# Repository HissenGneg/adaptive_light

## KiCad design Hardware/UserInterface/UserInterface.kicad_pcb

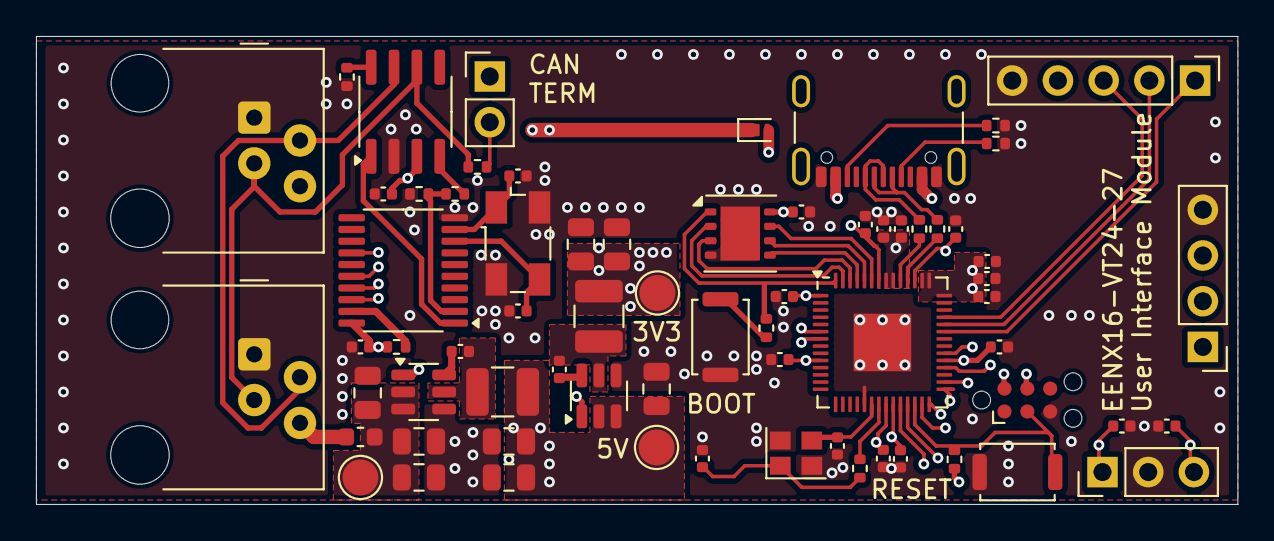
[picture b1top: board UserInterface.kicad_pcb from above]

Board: 4 copper layers, 66.8 x 26.0 mm, 68 parts (0 on the bottom side), 51 nets.

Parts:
C101, C102, C201, C202, C203, C204, C205, C206, C207, C208, C209, C211, C212, C213, C303, C304, C307, C311: 100n; C_0402_1005Metric
C210: 1u; C_0402_1005Metric
C214, C215, C305, C306: 10p; C_0402_1005Metric
C301, C302, C308, C312: 10u; C_0805_2012Metric
C309, C310, C313, C314: 22u; C_0805_2012Metric
D201: D_Schottky; Nexperia_DSN1608-2_1.6x0.8mm
F301: 4A; Fuse_0603_1608Metric
J101: conn_turnSignal; PinHeader_1x03_P2.54mm_Vertical
J102: conn_OLED; PinHeader_1x04_P2.54mm_Vertical
J103: conn_joystick; PinHeader_1x05_P2.54mm_Vertical
J201: TagConnect_SWD; Tag-Connect_TC2030-IDC-NL_2x03_P1.27mm_Vertical
J202: USB_C_Receptacle_USB2.0_16P; USB_C_Receptacle_GCT_USB4105-xx-A_16P_TopMnt_Horizontal
J301, J302: RJ9; RJ9_Evercom_5301-440xxx_Horizontal
JP301: Jumper_termination; PinHeader_1x02_P2.54mm_Vertical
L301, L302: 4u7; L_1210_3225Metric
R201, R202, R302: 5k1; R_0402_1005Metric
R203, R303, R304, R305: 10k; R_0402_1005Metric
R204, R207: 1k; R_0402_1005Metric
R205, R206: 27; R_0402_1005Metric
R301: 120; R_0402_1005Metric
SW201, SW202: SW_Push; SW_Push_SPST_NO_Alps_SKRK
TP301: TPVin; TestPoint_Pad_D2.0mm
TP302: TP3V3; TestPoint_Pad_D2.0mm
TP303: TP5V; TestPoint_Pad_D2.0mm
U201: W25Q64JVXGIQ; WSON-8-1EP_4x4mm_P0.8mm_EP2.2x3mm
U202: RP2040; QFN-56-1EP_7x7mm_P0.4mm_EP3.2x3.2mm
U301: MCP2551-I-SN; SOIC-8_3.9x4.9mm_P1.27mm
U302: MCP2515-xST; TSSOP-20_4.4x6.5mm_P0.65mm
U303: AP63203WU; TSOT-23-6
U304: AP63205WU; TSOT-23-6
Y201: 12M; Crystal_SMD_2520-4Pin_2.5x2.0mm
Y301: 8M; Crystal_SMD_Abracon_ABM3B-4Pin_5.0x3.2mm

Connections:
+1V1: C210.1, C211.1, C212.1, U202.23 (DVDD), U202.45 (VREG_VOUT), U202.50 (DVDD)
+3V3: C201.1, C202.1, C203.1, C204.1, C205.1, C206.1, C207.1, C208.1, C209.1, C213.1, C303.1, C309.1, C310.1, J102.3, J103.4, L301.2, R203.1, R305.1, TP302.1, U201.8 (VCC), U202.1 (IOVDD), U202.10 (IOVDD), U202.22 (IOVDD), U202.33 (IOVDD), U202.42 (IOVDD), U202.43 (ADC_AVDD), U202.44 (VREG_IN), U202.48 (USB_VDD), U202.49 (IOVDD), U302.20 (VDD), U303.1 (FB)
+5V: C304.1, C308.1, C313.1, C314.1, D201.1 (K), L302.2, TP303.1, U301.3 (VDD), U303.2 (EN), U303.3 (IN), U304.1 (FB)
+SYSTEM: C301.1, C302.1, C312.1, F301.2, TP301.1, U304.2 (EN), U304.3 (IN)
/BTN: J103.1, U202.37 (GPIO25)
/BTN_LEFT: C102.2, J101.3, U202.34 (GPIO22)
/BTN_RIGHT: C101.1, J101.1, U202.32 (GPIO21)
/CAN_Bus+power/CANH: J301.2, J302.2, JP301.1 (A), U301.7 (CANH)
/CAN_Bus+power/CANL: J301.3, J302.3, R301.2, U301.6 (CANL)
/MISO: U202.27 (GPIO16), U302.17 (SO)
/MOSI: U202.30 (GPIO19), U302.16 (SI)
/Microcontroller/FLASH_CLK: U201.6 (CLK), U202.52 (QSPI_SCLK)
/Microcontroller/FLASH_IO0: U201.5 (DI(IO0)), U202.53 (QSPI_SD0)
/Microcontroller/FLASH_IO1: U201.2 (DO(IO1)), U202.55 (QSPI_SD1)
/Microcontroller/FLASH_IO2: U201.3 (IO2), U202.54 (QSPI_SD2)
/Microcontroller/FLASH_IO3: U201.7 (IO3), U202.51 (QSPI_SD3)
/Microcontroller/FLASH_~CS: R204.2, U201.1 (~CS), U202.56 (QSPI_SS)
/Microcontroller/RP2040_D+: R205.2, U202.47 (USB_DP)
/Microcontroller/RP2040_D-: R206.2, U202.46 (USB_DM)
/Microcontroller/SWCLK: J201.4 (SWCLK), U202.24 (SWCLK)
/Microcontroller/SWD: J201.2 (SWDIO), U202.25 (SWD)
/Microcontroller/USB_D+: J202.A6 (D+), J202.B6 (D+), R205.1
/Microcontroller/USB_D-: J202.A7 (D-), J202.B7 (D-), R206.1
/Microcontroller/XIN: C214.2, U202.20 (XIN), Y201.3
/Microcontroller/XOUT: R207.2, U202.21 (XOUT)
/Microcontroller/XOUT_R: C215.2, R207.1, Y201.1
/Microcontroller/~RESET: J201.3 (~RESET), R203.2, SW201.1, U202.26 (RUN)
/SCK: U202.29 (GPIO18), U302.14 (SCK)
/SCL: J102.2, U202.7 (GPIO5)
/SDA: J102.1, U202.6 (GPIO4)
/VR_x: J103.3, U202.39 (GPIO27_ADC1)
/VR_y: J103.2, U202.38 (GPIO26_ADC0)
/~CS: U202.28 (GPIO17), U302.18 (~CS)
GND: C101.2, C102.1, C201.2, C202.2, C203.2, C204.2, C205.2, C206.2, C207.2, C208.2, C209.2, C210.2, C211.2, C212.2, C213.2, C214.1, C215.1, C301.2, C302.2, C303.2, C304.2, C305.1, C306.1, C308.2, C309.2, C310.2, C312.2, C313.2, C314.2, J101.2, J102.4, J103.5, J201.5 (GND), J202.A1 (GND), J202.A12 (GND), J202.B1 (GND), J202.B12 (GND), J301.1, J302.1, R201.2, R202.2, R303.2, R304.2, SW201.2, SW202.1, U201.4 (GND), U201.9 (EP), U202.19 (TESTEN), U202.57 (GND), U301.2 (VSS), U302.10 (VSS), U303.4 (GND), U304.4 (GND), Y201.2, Y201.4, Y301.2, Y301.4
unnamed: D201.2 (A), J202.A4 (VBUS), J202.A9 (VBUS), J202.B4 (VBUS), J202.B9 (VBUS)
unnamed: F301.1, J301.4, J302.4
unnamed: J202.A5 (CC1), R202.1
unnamed: J202.B5 (CC2), R201.1
unnamed: JP301.2 (B), R301.1
unnamed: R204.1, SW202.2
unnamed: R302.1, U301.4 (RXD)
unnamed: R304.1, U301.8 (Rs)
unnamed: U301.1 (TXD), U302.1 (TXCAN)
unnamed: C306.2, U302.9 (OSC1), Y301.1
unnamed: C305.2, U302.8 (OSC2), Y301.3
unnamed: R302.2, R303.1, U302.2 (RXCAN)
unnamed: R305.2, U302.19 (~RESET)
unnamed: C307.2, U303.6 (BST)
unnamed: C307.1, L301.1, U303.5 (SW)
unnamed: C311.2, U304.6 (BST)
unnamed: C311.1, L302.1, U304.5 (SW)

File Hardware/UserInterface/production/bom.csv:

Designator,Footprint,Quantity,Value,LCSC Part #
"C101, C102, C201, C202, C203, C204, C205, C206, C207, C208, C209, C211, C212, C213, C303, C304, C307, C311",0402,18,100n,
C210,0402,1,1u,
"C214, C215, C305, C306",0402,4,10p,
"C301, C302, C308, C312",0805,4,10u,
"C309, C310, C313, C314",0805,4,22u,
D201,Nexperia_DSN1608-2_1.6x0.8mm,1,D_Schottky,
F301,0603,1,4A,
J101,PinHeader_1x03_P2.54mm_Vertical,1,conn_turnSignal,
J102,PinHeader_1x04_P2.54mm_Vertical,1,conn_OLED,
J103,PinHeader_1x05_P2.54mm_Vertical,1,conn_joystick,
J202,USB_C_Receptacle_GCT_USB4105-xx-A_16P_TopMnt_Horizontal,1,USB_C_Receptacle_USB2.0_16P,
"J301, J302",RJ9_Evercom_5301-440xxx_Horizontal,2,RJ9,
JP301,PinHeader_1x02_P2.54mm_Vertical,1,Jumper_termination,
"L301, L302",1210,2,4u7,
"R201, R202, R302",0402,3,5k1,
"R203, R303, R304, R305",0402,4,10k,
"R204, R207",0402,2,1k,
"R205, R206",0402,2,27,
R301,0402,1,120,
"SW201, SW202",SW_Push_SPST_NO_Alps_SKRK,2,SW_Push,
TP301,TestPoint_Pad_D2.0mm,1,TPVin,
TP302,TestPoint_Pad_D2.0mm,1,TP3V3,
TP303,TestPoint_Pad_D2.0mm,1,TP5V,
U201,WSON-8-1EP_4x4mm_P0.8mm_EP2.2x3mm,1,W25Q64JVXGIQ,
U202,QFN-56-1EP_7x7mm_P0.4mm_EP3.2x3.2mm,1,RP2040,
U301,SOIC-8_3.9x4.9mm_P1.27mm,1,MCP2551-I-SN,
U302,TSSOP-20_4.4x6.5mm_P0.65mm,1,MCP2515-xST,
U303,TSOT-23-6,1,AP63203WU,
U304,TSOT-23-6,1,AP63205WU,
Y201,Crystal_SMD_2520-4Pin_2.5x2.0mm,1,12M,
Y301,Crystal_SMD_Abracon_ABM3B-4Pin_5.0x3.2mm,1,8M,

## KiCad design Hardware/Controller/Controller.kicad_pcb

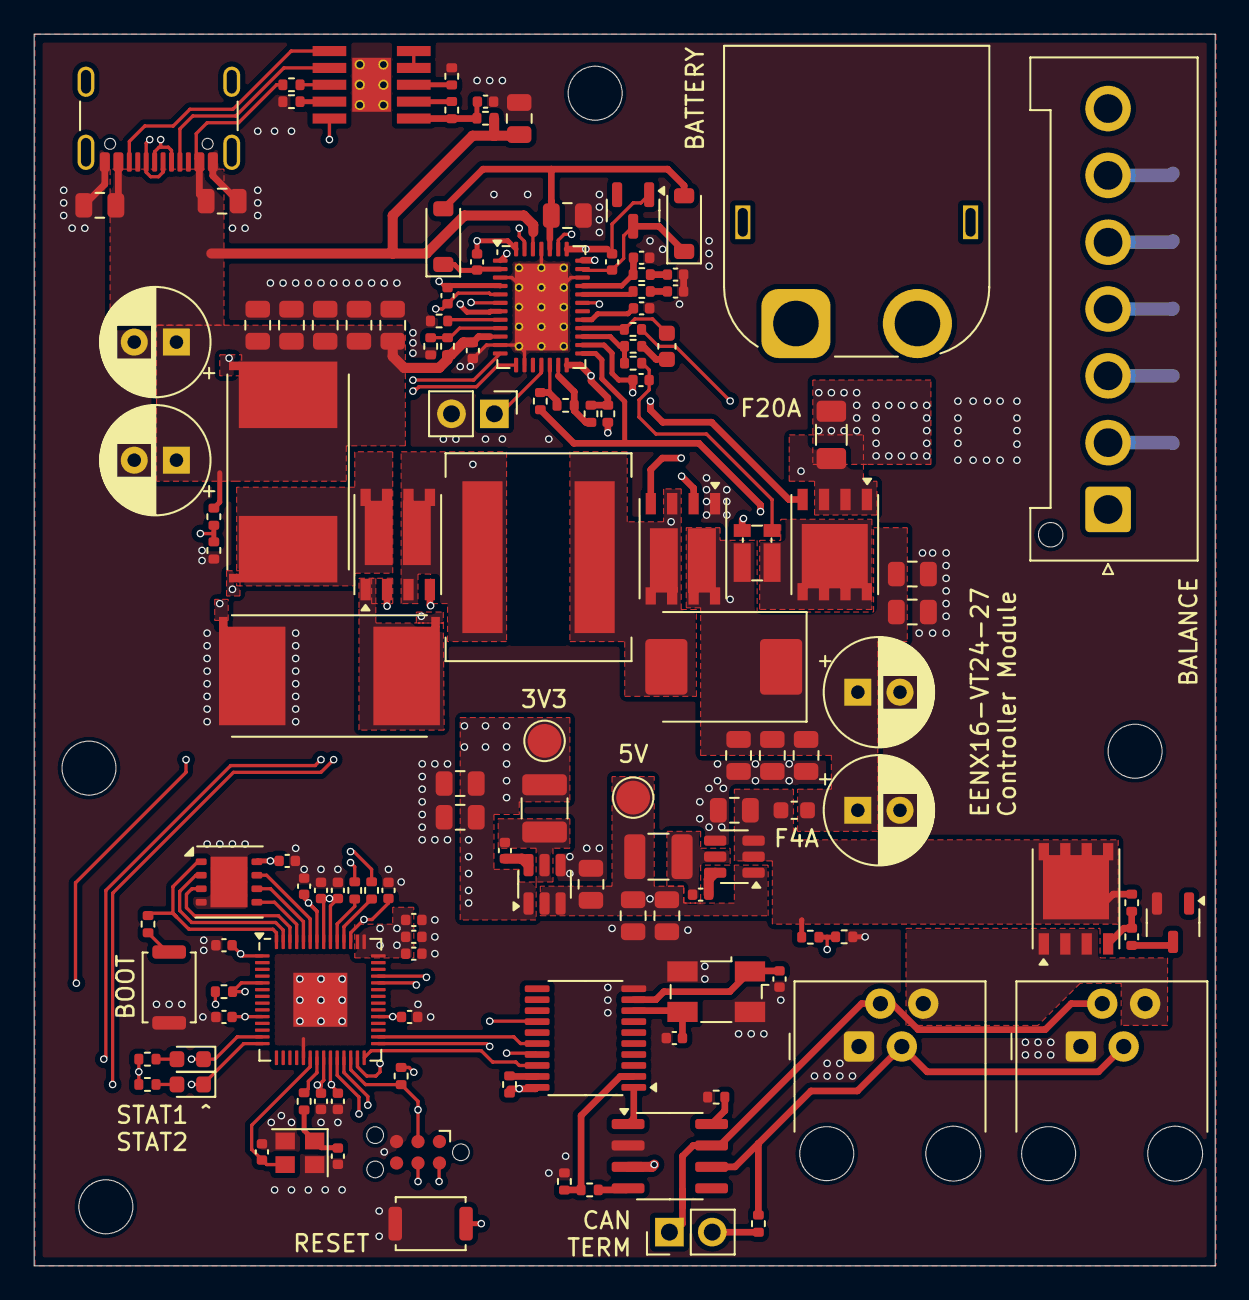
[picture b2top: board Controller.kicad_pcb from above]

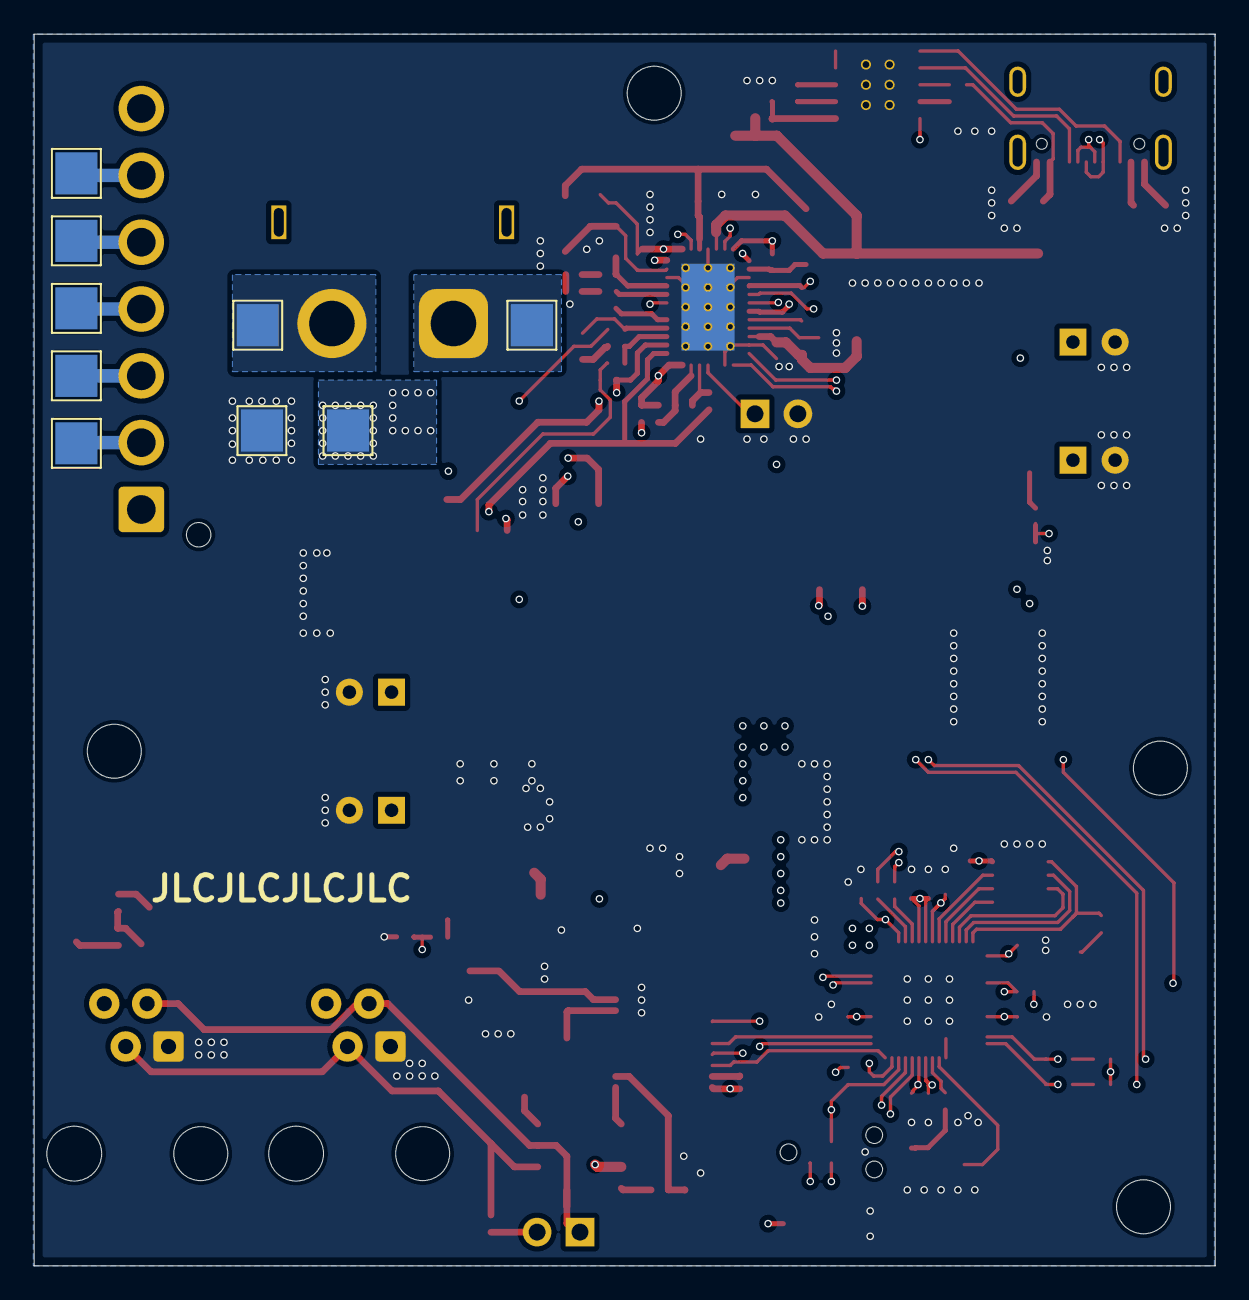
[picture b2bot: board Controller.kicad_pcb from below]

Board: 4 copper layers, 70.0 x 73.0 mm, 144 parts (9 on the bottom side), 102 nets.

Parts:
C201, C202, C203, C204, C205, C206, C207, C208, C209, C211, C212, C213, C401, C419, C432: 100n; C_0402_1005Metric
C210, C304, C423, C424: 1u; C_0402_1005Metric
C214, C215, C501, C502: 10p; C_0402_1005Metric
C301, C302, C303, C404, C405, C406, C407, C408, C409, C410, C411, C412, C413, C416, C420, C427: 10u; C_0805_2012Metric
C402, C403, C414, C415: 56u; CP_Radial_D6.3mm_P2.50mm
C417, C418, C421, C422: 22u; C_0805_2012Metric
C425: 2u2; C_0603_1608Metric
C426: 1n; C_0402_1005Metric
C428: 10n; C_0402_1005Metric
C429: 680p; C_0402_1005Metric
C430: 68p; C_0402_1005Metric
C431: 100p; C_0402_1005Metric
C433: 33n; C_0402_1005Metric
D401: MBRS360; D_SMC
D402: BZX84C6V2L; SOT-23
D403, D404: SBR0560S1; D_SOD-123
D405, D406: LED-GREEN; LED_0603_1608Metric
F401: 5A; Fuse_0603_1608Metric
F402: 20A; Fuse_1206_3216Metric
H101, H102, H103, H104: MountingHole; MountingHole_3.2mm_M3
J201: TagConnect_SWD; Tag-Connect_TC2030-IDC-NL_2x03_P1.27mm_Vertical
J301: USB_C_Receptacle_USB2.0_16P; USB_C_Receptacle_GCT_USB4105-xx-A_16P_TopMnt_Horizontal
J401: XT60; AMASS_XT60PW-M_1x02_P7.20mm_Horizontal
J402: Conn_balance; JST_VH_B7P-VH-FB-B_1x07_P3.96mm_Vertical
J403: Conn_NTC; PinHeader_1x02_P2.54mm_Vertical
J501, J502: RJ9; RJ9_Evercom_5301-440xxx_Horizontal
JP501: Jumper_termination; PinHeader_1x02_P2.54mm_Vertical
L401, L403: 4u7; L_1210_3225Metric
L402: XAL1010-153MED; L_Coilcraft_XAL1010-XXX
Q401, Q402: Si7252DP; PowerPAK_SO-8_Dual
Q403, Q501: Si7461DP; PowerPAK_SO-8_Single
Q502: Q_NMOS_GSD; SOT-23-3
R201, R302, R303, R304, R305, R306, R410, R420, R421, R501, R505, R506, R507: 10k; R_0402_1005Metric
R202, R205, R301, R416, R417, R418, R419: 1k; R_0402_1005Metric
R203, R204: 27; R_0402_1005Metric
R401, R402: 8m; R_Shunt_Vishay_WSR2_WSR3_KelvinConnection_4pins
R403, R408: 100; R_0402_1005Metric
R404: 105k; R_0402_1005Metric
R405, R406: 215k; R_0402_1005Metric
R407: 2m; R_Shunt_Vishay_WSKW0612
R409: 4R7; R_0402_1005Metric
R411, R412: 24k9; R_0402_1005Metric
R413: 100k; R_0402_1005Metric
R414: 56k; R_0402_1005Metric
R415: 47k; R_0402_1005Metric
R502, R504: 5k1; R_0402_1005Metric
R503: 120; R_0402_1005Metric
SW201, SW202: SW_Push; SW_Push_SPST_NO_Alps_SKRK
TP401: TP3V3; TestPoint_Pad_D2.0mm
TP402: TP5V; TestPoint_Pad_D2.0mm
TP403: BAT_S5; TestPoint_Pad_2.5x2.5mm
TP404: BAT_PROT+; TestPoint_Pad_2.5x2.5mm
TP405: BAT_UNPROT+; TestPoint_Pad_2.5x2.5mm
TP406: BAT_S4; TestPoint_Pad_2.5x2.5mm
TP407: BAT_PROT-; TestPoint_Pad_2.5x2.5mm
TP408: BAT_UNPROT-; TestPoint_Pad_2.5x2.5mm
TP409: BAT_S3; TestPoint_Pad_2.5x2.5mm
TP410: BAT_S2; TestPoint_Pad_2.5x2.5mm
TP411: BAT_S1; TestPoint_Pad_2.5x2.5mm
U201: W25Q64JVXGIQ; WSON-8-1EP_4x4mm_P0.8mm_EP2.2x3mm
U202: RP2040; QFN-56-1EP_7x7mm_P0.4mm_EP3.2x3.2mm
U301: CH224K; ESSOP10
U401: AP63203WU; TSOT-23-6
U402: AP63205WU; TSOT-23-6
U403: LTC4020; QFN-38-1EP_5x7mm_P0.5mm_EP3.15x5.15mm_ThermalVias
U501: MCP2551-I-SN; SOIC-8_3.9x4.9mm_P1.27mm
U502: MCP2515-xST; TSSOP-20_4.4x6.5mm_P0.65mm
Y201: 12M; Crystal_SMD_2520-4Pin_2.5x2.0mm
Y501: 8M; Crystal_SMD_Abracon_ABM3B-4Pin_5.0x3.2mm

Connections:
+1V1: C210.1, C211.1, C212.1, U202.23 (DVDD), U202.45 (VREG_VOUT), U202.50 (DVDD)
+3V3: C201.1, C202.1, C203.1, C204.1, C205.1, C206.1, C207.1, C208.1, C209.1, C213.1, C417.1, C418.1, L401.2, R201.1, R303.1, R416.1, R417.1, R507.1, TP401.1, U201.8 (VCC), U202.1 (IOVDD), U202.10 (IOVDD), U202.22 (IOVDD), U202.33 (IOVDD), U202.42 (IOVDD), U202.43 (ADC_AVDD), U202.44 (VREG_IN), U202.48 (USB_VDD), U202.49 (IOVDD), U401.1 (FB), U502.20 (VDD)
+5V: C416.1, C421.1, C422.1, L403.2, TP402.1, U401.2 (EN), U401.3 (IN), U402.1 (FB), U501.3 (VDD)
+SYSTEM: C420.1, F401.2, Q501.5 (D), R420.1, R501.1, U402.2 (EN), U402.3 (IN)
/BATTERY_MONITOR: R419.2, R420.2, U202.39 (GPIO27_ADC1)
/Battery/BAT: F402.1, Q403.1 (S), Q403.2 (S), Q403.3 (S), R406.1, U403.20 (BAT)
/Battery/BATT_RAW: C409.1, C410.1, C411.1, C412.1, C413.1, C414.1, C415.1, D401.1 (K), F401.1, Q402.5 (D), R405.1, R407.1
/Battery/BG1: Q401.2 (G), U403.37 (BG1)
/Battery/BG2: Q402.2 (G), U403.33 (BG2)
/Battery/BGATE: C426.2, Q403.4 (G), U403.21 (BGATE)
/Battery/BST1: C423.2, D403.1 (K), U403.2 (BST1)
/Battery/BST2: C424.1, D402.3 (K), D404.1 (K), U403.30 (BST2)
/Battery/CSN: R408.1, R409.2, U403.22 (CSN)
/Battery/CSOUT: C431.1, U403.24 (CSOUT)
/Battery/CSP: C425.1, R403.1, U403.23 (CSP)
/Battery/FBG: R411.2, R412.2, U403.18 (FBG)
/Battery/INTVcc: C427.1, D403.2 (A), D404.2 (A), U403.34 (INTVcc)
/Battery/ITH: R414.1, U403.27 (ITH)
/Battery/NTC: J403.1, U403.16 (NTC)
/Battery/RT: R413.1, U403.8 (RT)
/Battery/SENSBOT: C433.1, R402.2, U403.5 (SENSBOT)
/Battery/SENSGND: C433.2, R402.3, U403.4 (SENSGND)
/Battery/SENSTOP: R401.3, U403.6 (SENSTOP)
/Battery/SENSVin: R401.2, U403.7 (SENSVin)
/Battery/SHDN: R404.2, R410.1, U403.9 (SHDN)
/Battery/SW1: C423.1, L402.1, Q401.3 (S), Q401.6 (D), U403.38 (SW1)
/Battery/SW2: C424.2, D401.2 (A), D402.1 (A), L402.2, Q402.3 (S), Q402.6 (D), U403.32 (SW2)
/Battery/TG1: Q401.4 (G), U403.1 (TG1)
/Battery/TG2: Q402.4 (G), U403.31 (TG2)
/Battery/VC: C430.1, R415.1, U403.28 (VC)
/Battery/Vfb: R406.2, R412.1, U403.17 (Vfb)
/Battery/Vfb_minmax: R405.2, R411.1, U403.19 (Vfbmin), U403.26 (Vfbmax)
/CAN_bus/CANH: J501.2, J502.2, JP501.1 (A), U501.7 (CANH)
/CAN_bus/CANL: J501.3, J502.3, R503.2, U501.6 (CANL)
/MISO: U202.27 (GPIO16), U502.17 (SO)
/MOSI: U202.30 (GPIO19), U502.16 (SI)
/Microcontroller/FLASH_CLK: U201.6 (CLK), U202.52 (QSPI_SCLK)
/Microcontroller/FLASH_IO0: U201.5 (DI(IO0)), U202.53 (QSPI_SD0)
/Microcontroller/FLASH_IO1: U201.2 (DO(IO1)), U202.55 (QSPI_SD1)
/Microcontroller/FLASH_IO2: U201.3 (IO2), U202.54 (QSPI_SD2)
/Microcontroller/FLASH_IO3: U201.7 (IO3), U202.51 (QSPI_SD3)
/Microcontroller/FLASH_~CS: R202.2, U201.1 (~CS), U202.56 (QSPI_SS)
/Microcontroller/RP2040_D+: R203.2, U202.47 (USB_DP)
/Microcontroller/RP2040_D-: R204.2, U202.46 (USB_DM)
/Microcontroller/SWCLK: J201.4 (SWCLK), U202.24 (SWCLK)
/Microcontroller/SWD: J201.2 (SWDIO), U202.25 (SWD)
/Microcontroller/XIN: C214.2, U202.20 (XIN), Y201.3
/Microcontroller/XOUT: R205.2, U202.21 (XOUT)
/Microcontroller/XOUT_R: C215.2, R205.1, Y201.1
/Microcontroller/~RESET: J201.3 (~RESET), R201.2, SW201.1, U202.26 (RUN)
/PG: R303.2, U202.5 (GPIO3), U301.10 (PG)
/SCK: U202.29 (GPIO18), U502.14 (SCK)
/STAT1_OUT: D405.1 (K), U202.13 (GPIO10), U403.12 (STAT1)
/STAT2_OUT: D406.1 (K), U202.14 (GPIO11), U403.13 (STAT2)
/USBC/CC1: J301.A5 (CC1), U301.7 (CC1)
/USBC/CC2: J301.B5 (CC2), U301.6 (CC2)
/USBC/VDDCH: C304.1, R301.2, R304.1, U301.1 (VDD)
/USB_D+: J301.A6 (D+), J301.B6 (D+), R203.1
/USB_D-: J301.A7 (D-), J301.B7 (D-), R204.1
/VBUS_MONITOR: R418.2, R421.2, U202.38 (GPIO26_ADC0)
/~CS: U202.28 (GPIO17), U502.18 (~CS)
GND: C201.2, C202.2, C203.2, C204.2, C205.2, C206.2, C207.2, C208.2, C209.2, C210.2, C211.2, C212.2, C213.2, C214.1, C215.1, C301.2, C302.2, C303.2, C304.2, C402.2, C403.2, C404.2, C405.2, C406.2, C407.2, C408.2, C409.2, C410.2, C411.2, C412.2, C413.2, C414.2, C415.2, C416.2, C417.2, C418.2, C420.2, C421.2, C422.2, C427.2, C428.2, C429.2, C430.2, C431.2, C432.2, C501.1, C502.1, J201.5 (GND), J301.A1 (GND), J301.A12 (GND), J301.B1 (GND), J301.B12 (GND), J403.2, J501.1, J502.1, Q402.1 (S), Q502.2 (S), R305.2, R306.2, R402.4, R410.2, R413.2, R418.1, R419.1, R505.2, R506.2, SW201.2, SW202.1, TP407.1, U201.4 (GND), U201.9 (EP), U202.19 (TESTEN), U202.57 (GND), U301.11 (GND), U401.4 (GND), U402.4 (GND), U403.3 (SGND), U403.11 (MODE), U403.14 (TIMER), U403.29 (SGND), U403.35 (PGND), U403.39 (GND), U501.2 (VSS), U502.10 (VSS), Y201.2, Y201.4, Y501.2, Y501.4
unnamed: C425.2, R409.1
unnamed: C426.1, R407.3, R408.2
unnamed: C428.1, R414.2
unnamed: C429.1, R415.2
unnamed: D405.2 (A), R416.2
unnamed: D406.2 (A), R417.2
unnamed: F402.2, TP404.1
unnamed: J401.1, TP408.1
unnamed: J401.2, TP405.1
unnamed: J402.2, TP411.1
unnamed: J402.3, TP410.1
unnamed: J402.4, TP409.1
unnamed: J402.5, TP406.1
unnamed: J402.6, TP403.1
unnamed: J501.4, J502.4, Q501.1 (S), Q501.2 (S), Q501.3 (S)
unnamed: JP501.2 (B), R503.1
unnamed: Q401.1 (S), R402.1
unnamed: Q401.5 (D), R401.4
unnamed: Q403.5 (D), R407.4
unnamed: Q501.4 (G), R501.2, R502.1
unnamed: Q502.3 (D), R502.2
unnamed: R202.1, SW202.2
unnamed: R403.2, R407.2
unnamed: R306.1, U301.9 (CFG1)
unnamed: R304.2, U301.2 (CFG2)
unnamed: R305.1, U301.3 (CFG3)
unnamed: U301.4 (DP), U301.5 (DM)
unnamed: R302.2, U301.8 (VBUS)
unnamed: C401.2, U401.6 (BST)
unnamed: C401.1, L401.1, U401.5 (SW)
unnamed: C419.2, U402.6 (BST)
unnamed: C419.1, L403.1, U402.5 (SW)
unnamed: R504.1, U501.4 (RXD)
unnamed: R506.1, U501.8 (Rs)
unnamed: U501.1 (TXD), U502.1 (TXCAN)
unnamed: C502.2, U502.9 (OSC1), Y501.1
unnamed: C501.2, U502.8 (OSC2), Y501.3
unnamed: R504.2, R505.1, U502.2 (RXCAN)
unnamed: R507.2, U502.19 (~RESET)
VBUS: C301.1, C302.1, C303.1, C402.1, C403.1, C404.1, C405.1, C406.1, C407.1, C408.1, C432.1, J301.A4 (VBUS), J301.A9 (VBUS), J301.B4 (VBUS), J301.B9 (VBUS), R301.1, R302.1, R401.1, R404.1, R421.1, U403.10 (Vin_reg), U403.36 (PVin)

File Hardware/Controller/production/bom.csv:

Designator,Footprint,Quantity,Value,LCSC Part #
"C201, C202, C203, C204, C205, C206, C207, C208, C209, C211, C212, C213, C401, C419, C432",0402,15,100n,
"C210, C304, C423, C424",0402,4,1u,
"C214, C215, C501, C502",0402,4,10p,
"C301, C302, C303, C404, C405, C406, C407, C408, C409, C410, C411, C412, C413, C416, C420, C427",0805,16,10u,
"C402, C403, C414, C415",CP_Radial_D6.3mm_P2.50mm,4,56u,
"C417, C418, C421, C422",0805,4,22u,
C425,0603,1,2u2,
C426,0402,1,1n,
C428,0402,1,10n,
C429,0402,1,680p,
C430,0402,1,68p,
C431,0402,1,100p,
C433,0402,1,33n,
D401,D_SMC,1,MBRS360,
D402,SOT-23,1,BZX84C6V2L,
"D403, D404",D_SOD-123,2,SBR0560S1,
"D405, D406",0603,2,LED-GREEN,
F401,0603,1,5A,
F402,1206,1,20A,
"H101, H102, H103, H104",MountingHole_3.2mm_M3,4,MountingHole,
J301,USB_C_Receptacle_GCT_USB4105-xx-A_16P_TopMnt_Horizontal,1,USB_C_Receptacle_USB2.0_16P,
J401,AMASS_XT60PW-M_1x02_P7.20mm_Horizontal,1,XT60,
J402,JST_VH_B7P-VH-FB-B_1x07_P3.96mm_Vertical,1,Conn_balance,
J403,PinHeader_1x02_P2.54mm_Vertical,1,Conn_NTC,
"J501, J502",RJ9_Evercom_5301-440xxx_Horizontal,2,RJ9,
JP501,PinHeader_1x02_P2.54mm_Vertical,1,Jumper_termination,
"L401, L403",1210,2,4u7,
L402,L_Coilcraft_XAL1010-XXX,1,XAL1010-153MED,
"Q401, Q402",PowerPAK_SO-8_Dual,2,Si7252DP,
"Q403, Q501",PowerPAK_SO-8_Single,2,Si7461DP,
"R201, R302, R303, R304, R305, R306, R410, R420, R421, R501, R505, R506, R507",0402,13,10k,
"R202, R205, R301, R416, R417, R418, R419",0402,7,1k,
"R203, R204",0402,2,27,
"R401, R402",R_Shunt_Vishay_WSR2_WSR3_KelvinConnection_4pins,2,8m,
"R403, R408",0402,2,100,
R404,0402,1,105k,
"R405, R406",0402,2,215k,
R407,R_Shunt_Vishay_WSKW0612,1,2m,
R409,0402,1,4R7,
"R411, R412",0402,2,24k9,
R413,0402,1,100k,
R414,0402,1,56k,
R415,0402,1,47k,
"R502, R504",0402,2,5k1,
R503,0402,1,120,
"SW201, SW202",SW_Push_SPST_NO_Alps_SKRK,2,SW_Push,
TP401,TestPoint_Pad_D2.0mm,1,TP3V3,
TP402,TestPoint_Pad_D2.0mm,1,TP5V,
TP403,TestPoint_Pad_2.5x2.5mm,1,BAT_S5,
TP404,TestPoint_Pad_2.5x2.5mm,1,BAT_PROT+,
TP405,TestPoint_Pad_2.5x2.5mm,1,BAT_UNPROT+,
TP406,TestPoint_Pad_2.5x2.5mm,1,BAT_S4,
TP407,TestPoint_Pad_2.5x2.5mm,1,BAT_PROT-,
TP408,TestPoint_Pad_2.5x2.5mm,1,BAT_UNPROT-,
TP409,TestPoint_Pad_2.5x2.5mm,1,BAT_S3,
TP410,TestPoint_Pad_2.5x2.5mm,1,BAT_S2,
TP411,TestPoint_Pad_2.5x2.5mm,1,BAT_S1,
U201,WSON-8-1EP_4x4mm_P0.8mm_EP2.2x3mm,1,W25Q64JVXGIQ,
U202,QFN-56-1EP_7x7mm_P0.4mm_EP3.2x3.2mm,1,RP2040,
U301,ESSOP10,1,CH224K,
U401,TSOT-23-6,1,AP63203WU,
U402,TSOT-23-6,1,AP63205WU,
U403,QFN-38-1EP_5x7mm_P0.5mm_EP3.15x5.15mm_ThermalVias,1,LTC4020,
U501,SOIC-8_3.9x4.9mm_P1.27mm,1,MCP2551-I-SN,
U502,TSSOP-20_4.4x6.5mm_P0.65mm,1,MCP2515-xST,
Y201,Crystal_SMD_2520-4Pin_2.5x2.0mm,1,12M,
Y501,Crystal_SMD_Abracon_ABM3B-4Pin_5.0x3.2mm,1,8M,

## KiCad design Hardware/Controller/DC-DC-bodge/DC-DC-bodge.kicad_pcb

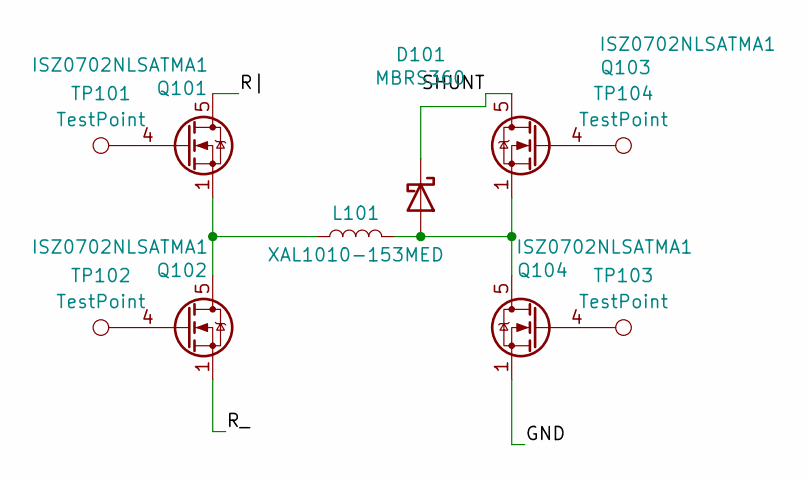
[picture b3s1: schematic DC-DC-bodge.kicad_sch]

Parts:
D101: MBRS360; D_SMC; mouser 78-VS-MBRS360-M39AT
L101: XAL1010-153MED; L_Coilcraft_XAL1010-XXX; mouser 994-XAL1010-153MED
Q101, Q102, Q103, Q104: ISZ0702NLSATMA1; VSON-8_3.3x3.3mm_P0.65mm_NexFET_not_very_fucking_stupid_as_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; mouser 726-ISZ0702NLSATMA1
TP101, TP102, TP103, TP104: TestPoint; TestPoint_Pad_2.0x2.0mm

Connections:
/GND: Q104.1 (S), Q104.2 (S), Q104.3 (S)
/R_: Q102.1 (S), Q102.2 (S), Q102.3 (S)
/R|: Q101.5 (D)
/SHUNT: D101.1 (K), Q103.5 (D)
unnamed: D101.2 (A), L101.2, Q103.1 (S), Q103.2 (S), Q103.3 (S), Q104.5 (D)
unnamed: Q101.4 (G), TP101.1
unnamed: L101.1, Q101.1 (S), Q101.2 (S), Q101.3 (S), Q102.5 (D)
unnamed: Q102.4 (G), TP102.1
unnamed: Q103.4 (G), TP104.1
unnamed: Q104.4 (G), TP103.1

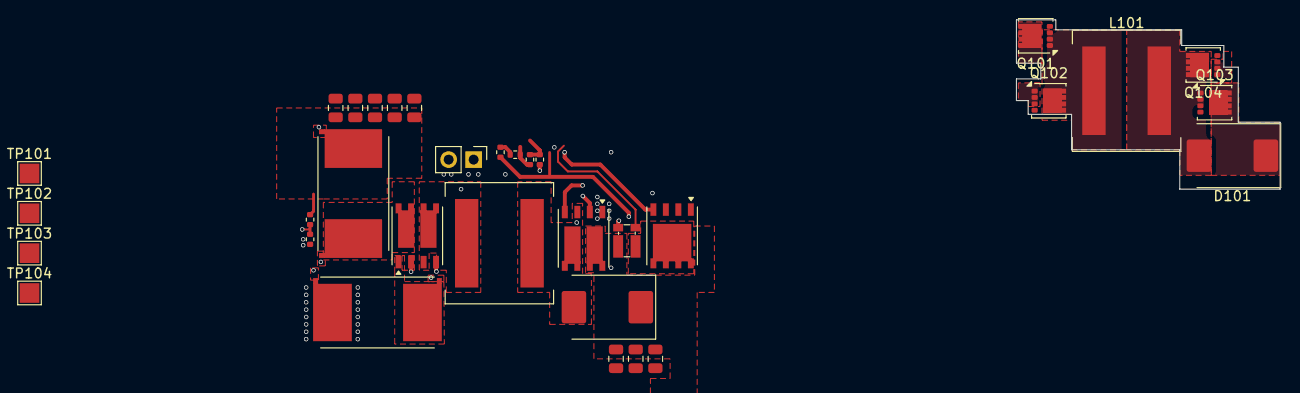
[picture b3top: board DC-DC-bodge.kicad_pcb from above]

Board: 2 copper layers, 26.8 x 17.2 mm, 33 parts (0 on the bottom side), 9 nets.

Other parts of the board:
C404, C405, C406, C407, C408, C409, C410, C411: 10u; C_0805_2012Metric
D401: MBRS360; D_SMC
J403: Conn_NTC; PinHeader_1x02_P2.54mm_Vertical
L402: XAL1010-153MED; L_Coilcraft_XAL1010-XXX
Q401, Q402: Si7252DP; PowerPAK_SO-8_Dual
Q403: Si7461DP; PowerPAK_SO-8_Single
R401, R402: 8m; R_Shunt_Vishay_WSR2_WSR3_KelvinConnection_4pins
R405, R406: 215k; R_0402_1005Metric
R407: 2m; R_Shunt_Vishay_WSKW0612
R411, R412: 24k9; R_0402_1005Metric
R418: 1k; R_0402_1005Metric
R421: 10k; R_0402_1005Metric
